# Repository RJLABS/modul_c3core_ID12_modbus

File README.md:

# modul_c3core_ID12_modbus

## Image Rendering

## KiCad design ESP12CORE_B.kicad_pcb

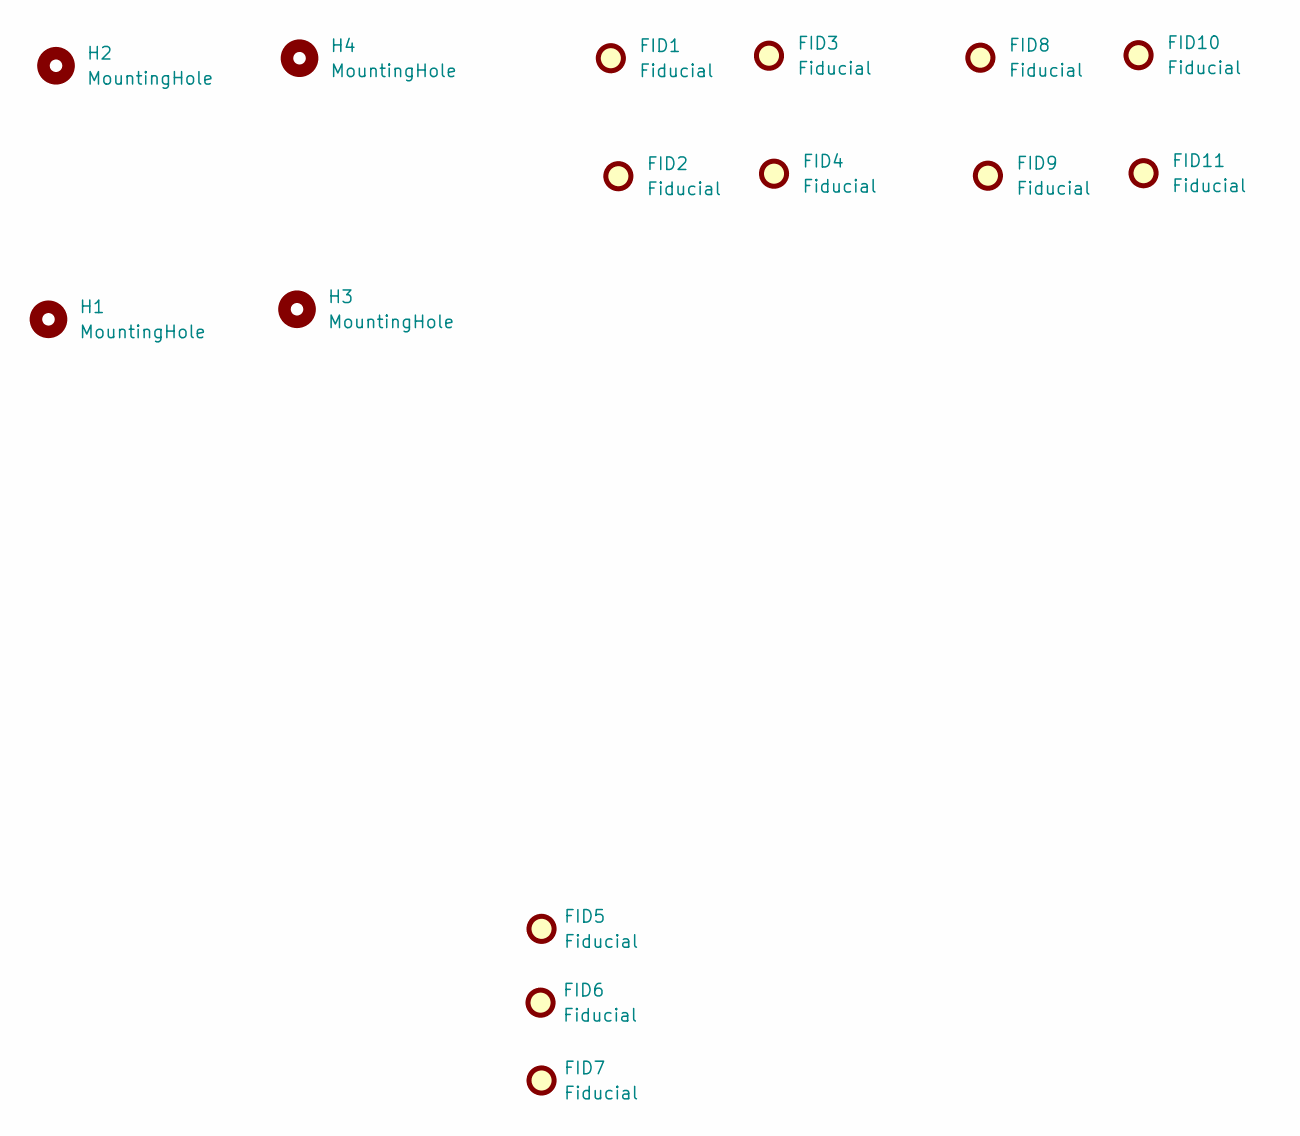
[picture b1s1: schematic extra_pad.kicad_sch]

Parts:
FID1, FID2, FID3, FID4, FID8, FID9, FID10, FID11: Fiducial; mouse-bite-2mm-slot
FID5, FID6, FID7: Fiducial; Fiducial_0.75mm_Mask1.5mm
H1, H2, H3, H4: MountingHole; MountingHole_3.2mm_M3_Pad_Via

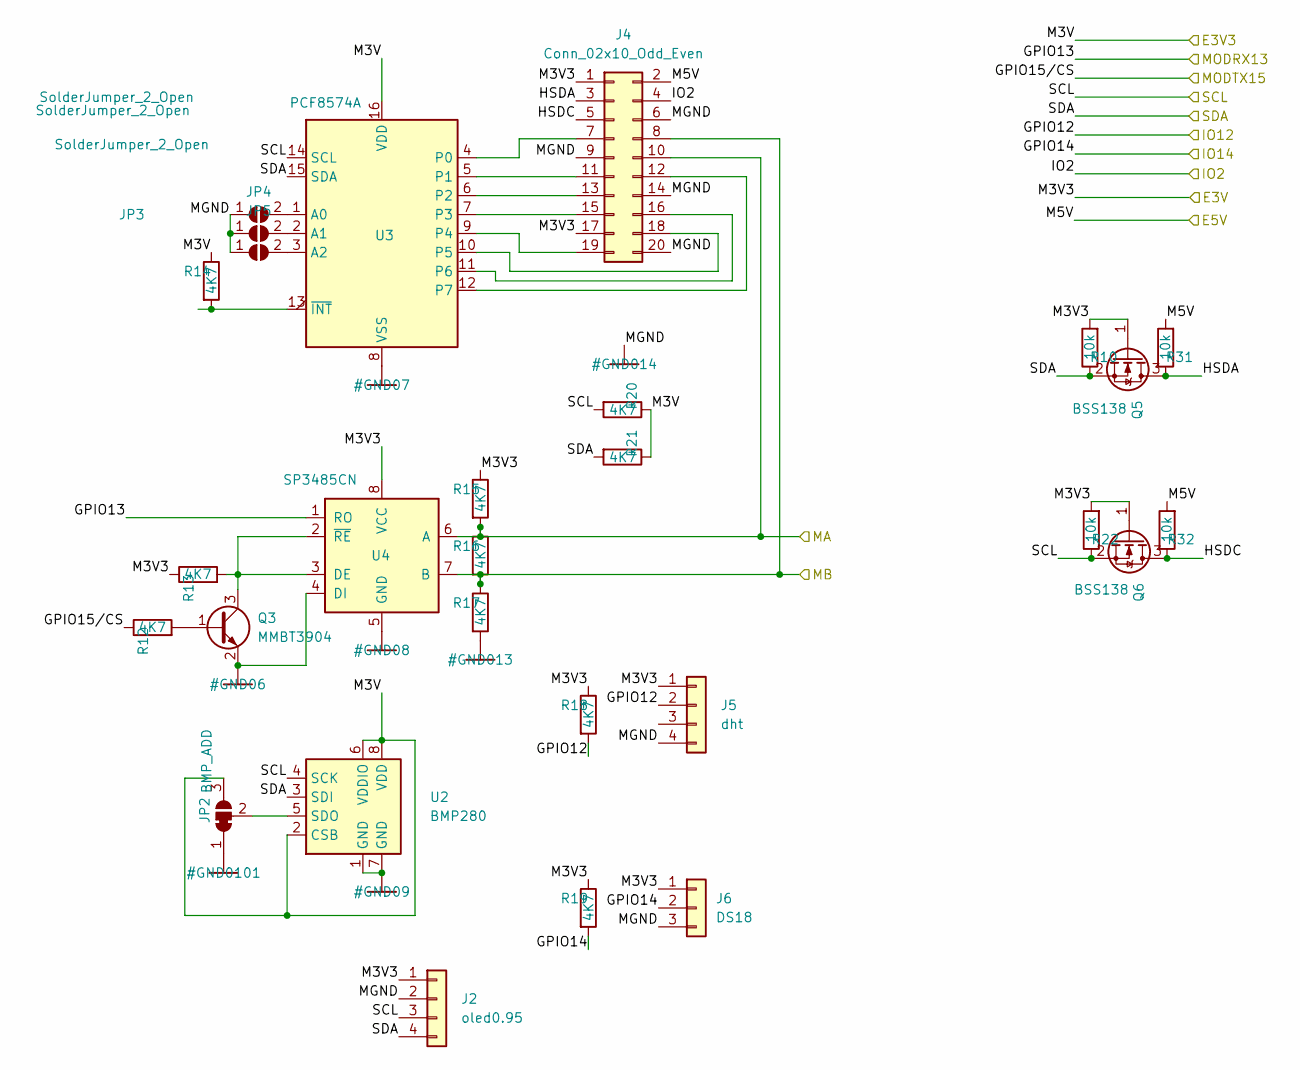
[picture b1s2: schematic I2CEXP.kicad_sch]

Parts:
J2: oled0.95; PinHeader_1x04_P2.54mm_Vertical
J4: Conn_02x10_Odd_Even; IDC-Header_2x10_P2.54mm_Vertical
J5: dht; PinHeader_1x04_P2.54mm_Vertical
J6: DS18; PinHeader_1x03_P2.54mm_Vertical
JP2: BMP_ADD; SolderJumper-3_P1.3mm_Bridged12_RoundedPad1.0x1.5mm
JP3, JP4, JP5: SolderJumper_2_Open; SolderJumper-2_P1.3mm_Open_RoundedPad1.0x1.5mm
Q3: MMBT3904; SOT-23
Q5, Q6: BSS138; SOT-23
R10, R22, R31, R32: 10k; R_0805_2012Metric
R12, R13, R14, R15, R16, R17, R18, R19, R20, R21: 4K7; R_0805_2012Metric
U2: BMP280; Bosch_LGA-8_2x2.5mm_P0.65mm_ClockwisePinNumbering
U3: PCF8574A; SOIC-16W_7.5x10.3mm_P1.27mm
U4: SP3485CN; SOIC-8_3.9x4.9mm_P1.27mm

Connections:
/CPU_ESP12F/EVCC: J2.1, J4.1, J4.17, J5.1, J6.1, Q5.1 (G), Q6.1 (G), R10.2, R13.1, R15.1, R18.1, R19.1, R22.2, U4.8 (VCC); also elsewhere on the board
/CPU_ESP12F/GPIO2: J4.4; also elsewhere on the board
/CPU_ESP12F/GPIO4/SDA: J2.4, Q5.2 (S), R10.1, R21.2, U2.3 (SDI), U3.15 (SDA); also elsewhere on the board
/CPU_ESP12F/GPIO5/SCL: J2.3, Q6.2 (S), R20.2, R22.1, U2.4 (SCK), U3.14 (SCL); also elsewhere on the board
/CPU_ESP12F/GPIO12/MISO: J5.2, R18.2; also elsewhere on the board
/CPU_ESP12F/GPIO13/MOSI: U4.1 (RO); also elsewhere on the board
/CPU_ESP12F/GPIO14/SCK: J6.2, R19.2; also elsewhere on the board
/CPU_ESP12F/GPIO15/CS: R12.1; also elsewhere on the board
/CPU_ESP12F/VCC: JP2.3 (B), R14.1, R20.1, R21.1, U2.2 (CSB), U2.6 (VDDIO), U2.8 (VDD), U3.16 (VDD); also elsewhere on the board
/EXTENTION/HSDA: J4.3, Q5.3 (D), R31.1
/EXTENTION/HSDC: J4.5, Q6.3 (D), R32.1
/EXTENTION/M5V: J4.2, R31.2, R32.2; also elsewhere on the board
/EXTENTION/MA: J4.10, R15.2, R16.1, U4.6 (A); also elsewhere on the board
/EXTENTION/MB: J4.8, R16.2, R17.1, U4.7 (B); also elsewhere on the board
GND: J2.2, J4.6, J4.9, J4.14, J4.20, J5.4, J6.3, JP2.1 (A), JP3.1 (A), JP4.1 (A), JP5.1 (A), Q3.2 (E), R17.2, U2.1 (GND), U2.7 (GND), U3.8 (VSS), U4.4 (DI), U4.5 (GND); also elsewhere on the board
unnamed: J4.7, U3.4 (P0)
unnamed: J4.11, U3.5 (P1)
unnamed: J4.12, U3.12 (P7)
unnamed: J4.13, U3.6 (P2)
unnamed: J4.15, U3.7 (P3)
unnamed: J4.16, U3.11 (P6)
unnamed: J4.18, U3.10 (P5)
unnamed: J4.19, U3.9 (P4)
unnamed: JP2.2 (C), U2.5 (SDO)
unnamed: JP3.2 (B), U3.1 (A0)
unnamed: JP4.2 (B), U3.2 (A1)
unnamed: JP5.2 (B), U3.3 (A2)
unnamed: Q3.1 (B), R12.2
unnamed: Q3.3 (C), R13.2, U4.2 (~RE), U4.3 (DE)
unnamed: R14.2, U3.13 (~INT)

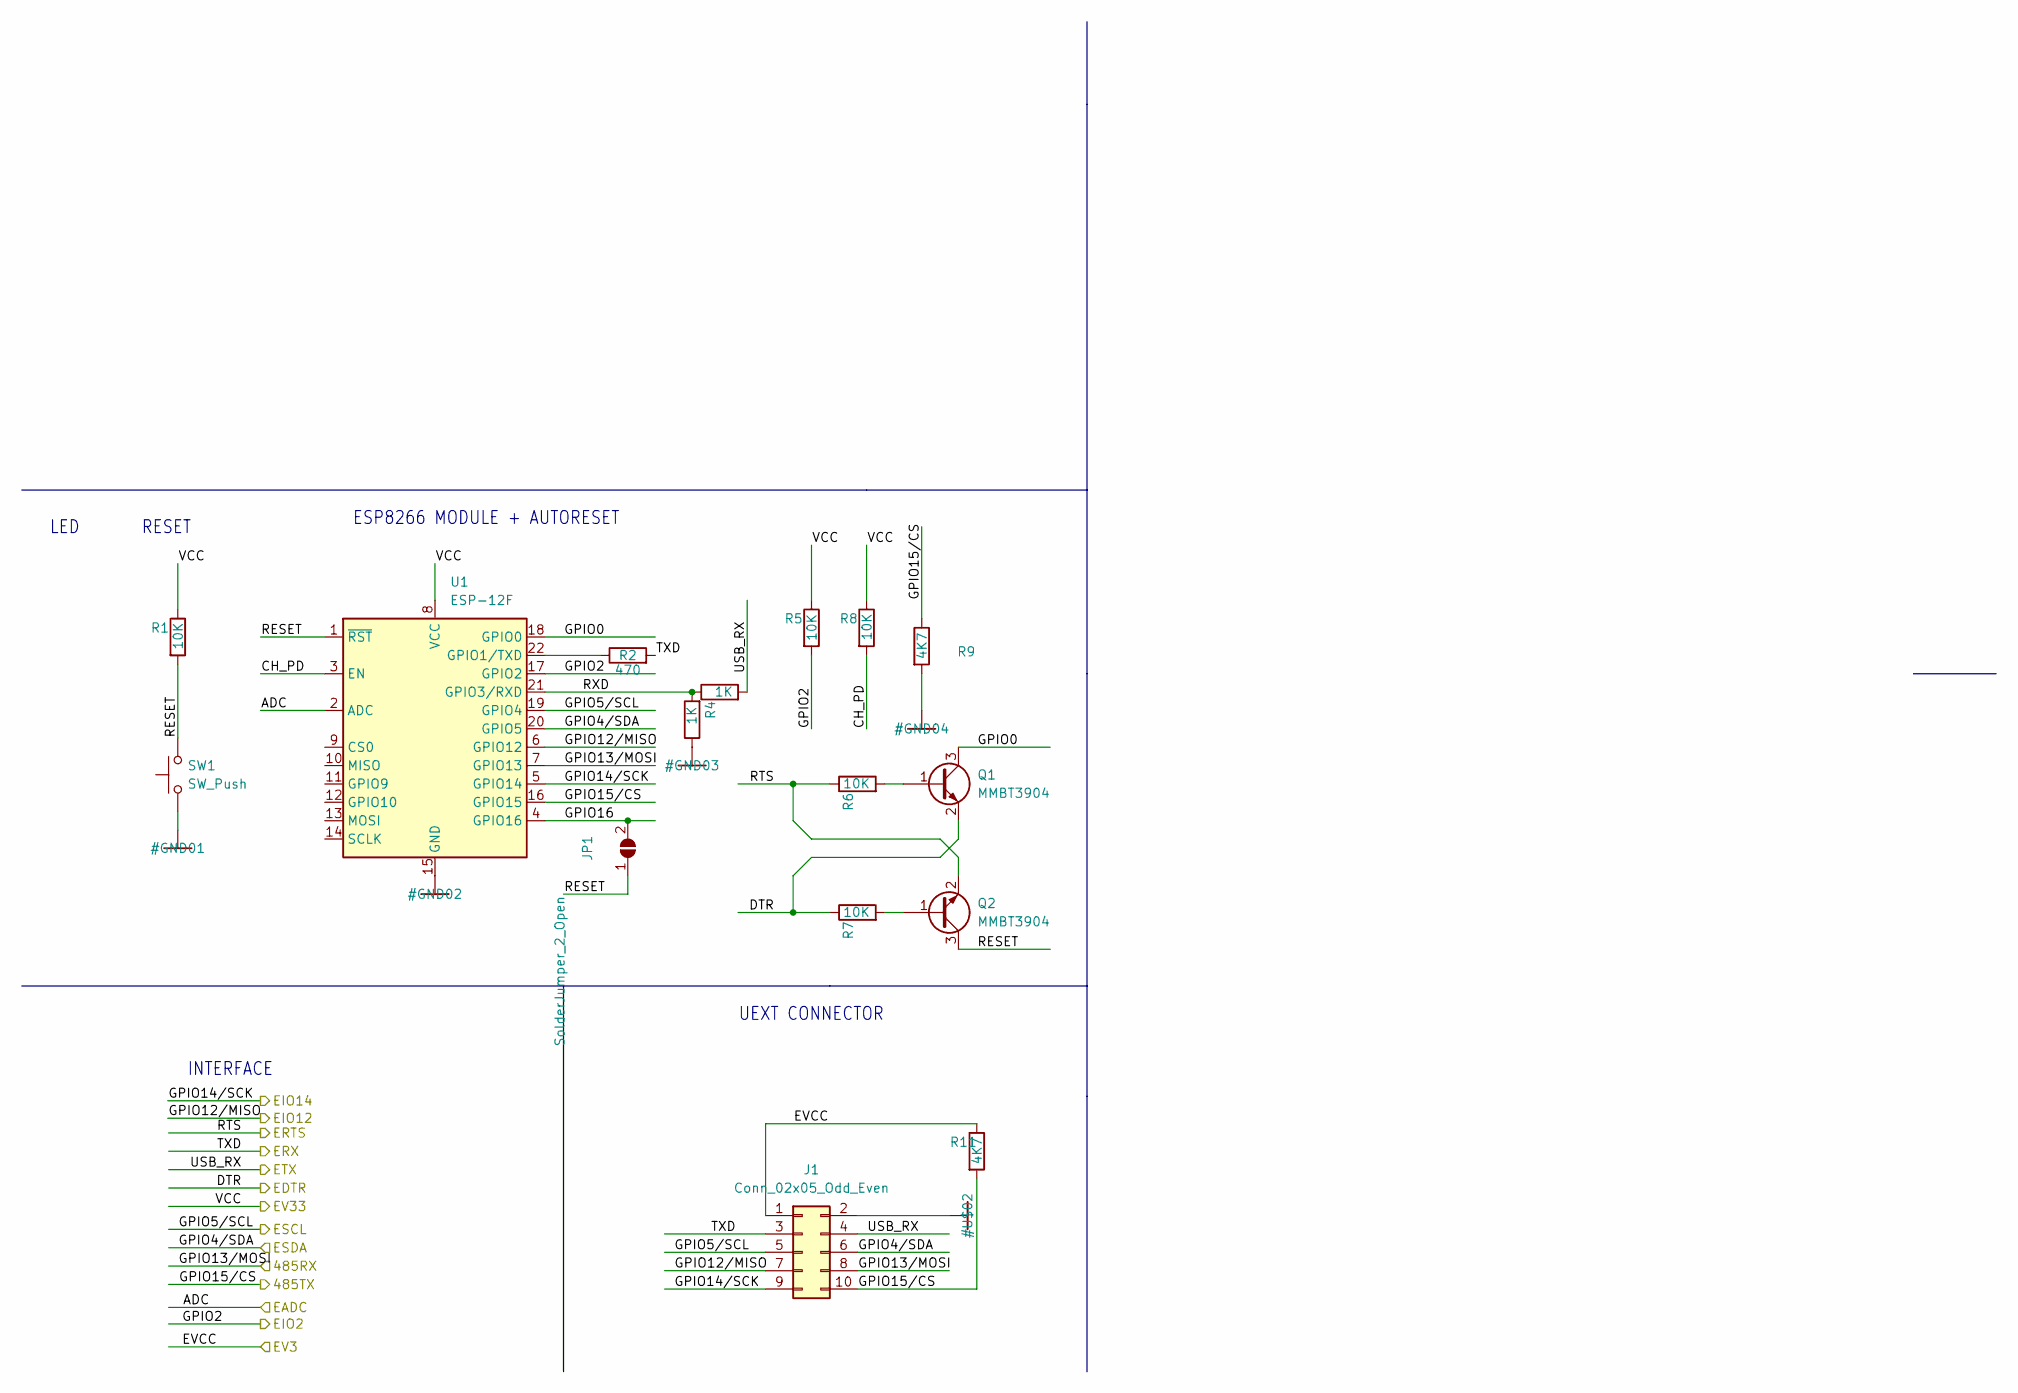
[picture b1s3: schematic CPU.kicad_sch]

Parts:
J1: Conn_02x05_Odd_Even; IDC-Header_2x05_P2.54mm_Vertical
JP1: SolderJumper_2_Open; SolderJumper-2_P1.3mm_Open_RoundedPad1.0x1.5mm
Q1, Q2: MMBT3904; SOT-23
R1, R5, R6, R7, R8: 10K; R_0805_2012Metric
R2: 470; R_0805_2012Metric
R3, R4: 1K; R_0805_2012Metric
R9, R11: 4K7; R_0805_2012Metric
SW1: SW_Push; SW_SPST_B3U-1000P-B
U1: ESP-12F; ESP-12E

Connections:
/CPU_ESP12F/ADC: U1.2 (ADC); also elsewhere on the board
/CPU_ESP12F/CH_PD: R8.2, U1.3 (EN)
/CPU_ESP12F/DTR: Q1.2 (E), R7.1; also elsewhere on the board
/CPU_ESP12F/EVCC: J1.1, R11.1; also elsewhere on the board
/CPU_ESP12F/GPIO0: Q1.3 (C), U1.18 (GPIO0)
/CPU_ESP12F/GPIO2: R5.2, U1.17 (GPIO2); also elsewhere on the board
/CPU_ESP12F/GPIO4/SDA: J1.6, U1.20 (GPIO5); also elsewhere on the board
/CPU_ESP12F/GPIO5/SCL: J1.5, U1.19 (GPIO4); also elsewhere on the board
/CPU_ESP12F/GPIO12/MISO: J1.7, U1.6 (GPIO12); also elsewhere on the board
/CPU_ESP12F/GPIO13/MOSI: J1.8, U1.7 (GPIO13); also elsewhere on the board
/CPU_ESP12F/GPIO14/SCK: J1.9, U1.5 (GPIO14); also elsewhere on the board
/CPU_ESP12F/GPIO15/CS: J1.10, R9.1, R11.2, U1.16 (GPIO15); also elsewhere on the board
/CPU_ESP12F/GPIO16: JP1.2 (B), U1.4 (GPIO16)
/CPU_ESP12F/RXD: R3.2, R4.1, U1.21 (GPIO3/RXD)
/CPU_ESP12F/TXD: J1.3, R2.2; also elsewhere on the board
/CPU_ESP12F/USB_RX: J1.4, R4.2; also elsewhere on the board
/CPU_ESP12F/VCC: R1.1, R5.1, R8.1, U1.8 (VCC); also elsewhere on the board
GND: J1.2, R3.1, R9.2, SW1.1, U1.15 (GND); also elsewhere on the board
unnamed: Q1.1 (B), R6.2
unnamed: Q2.1 (B), R7.2
unnamed: R2.1, U1.22 (GPIO1/TXD)

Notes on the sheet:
UEXT CONNECTOR
LED
INTERFACE
ESP8266 MODULE + AUTORESET
RESET

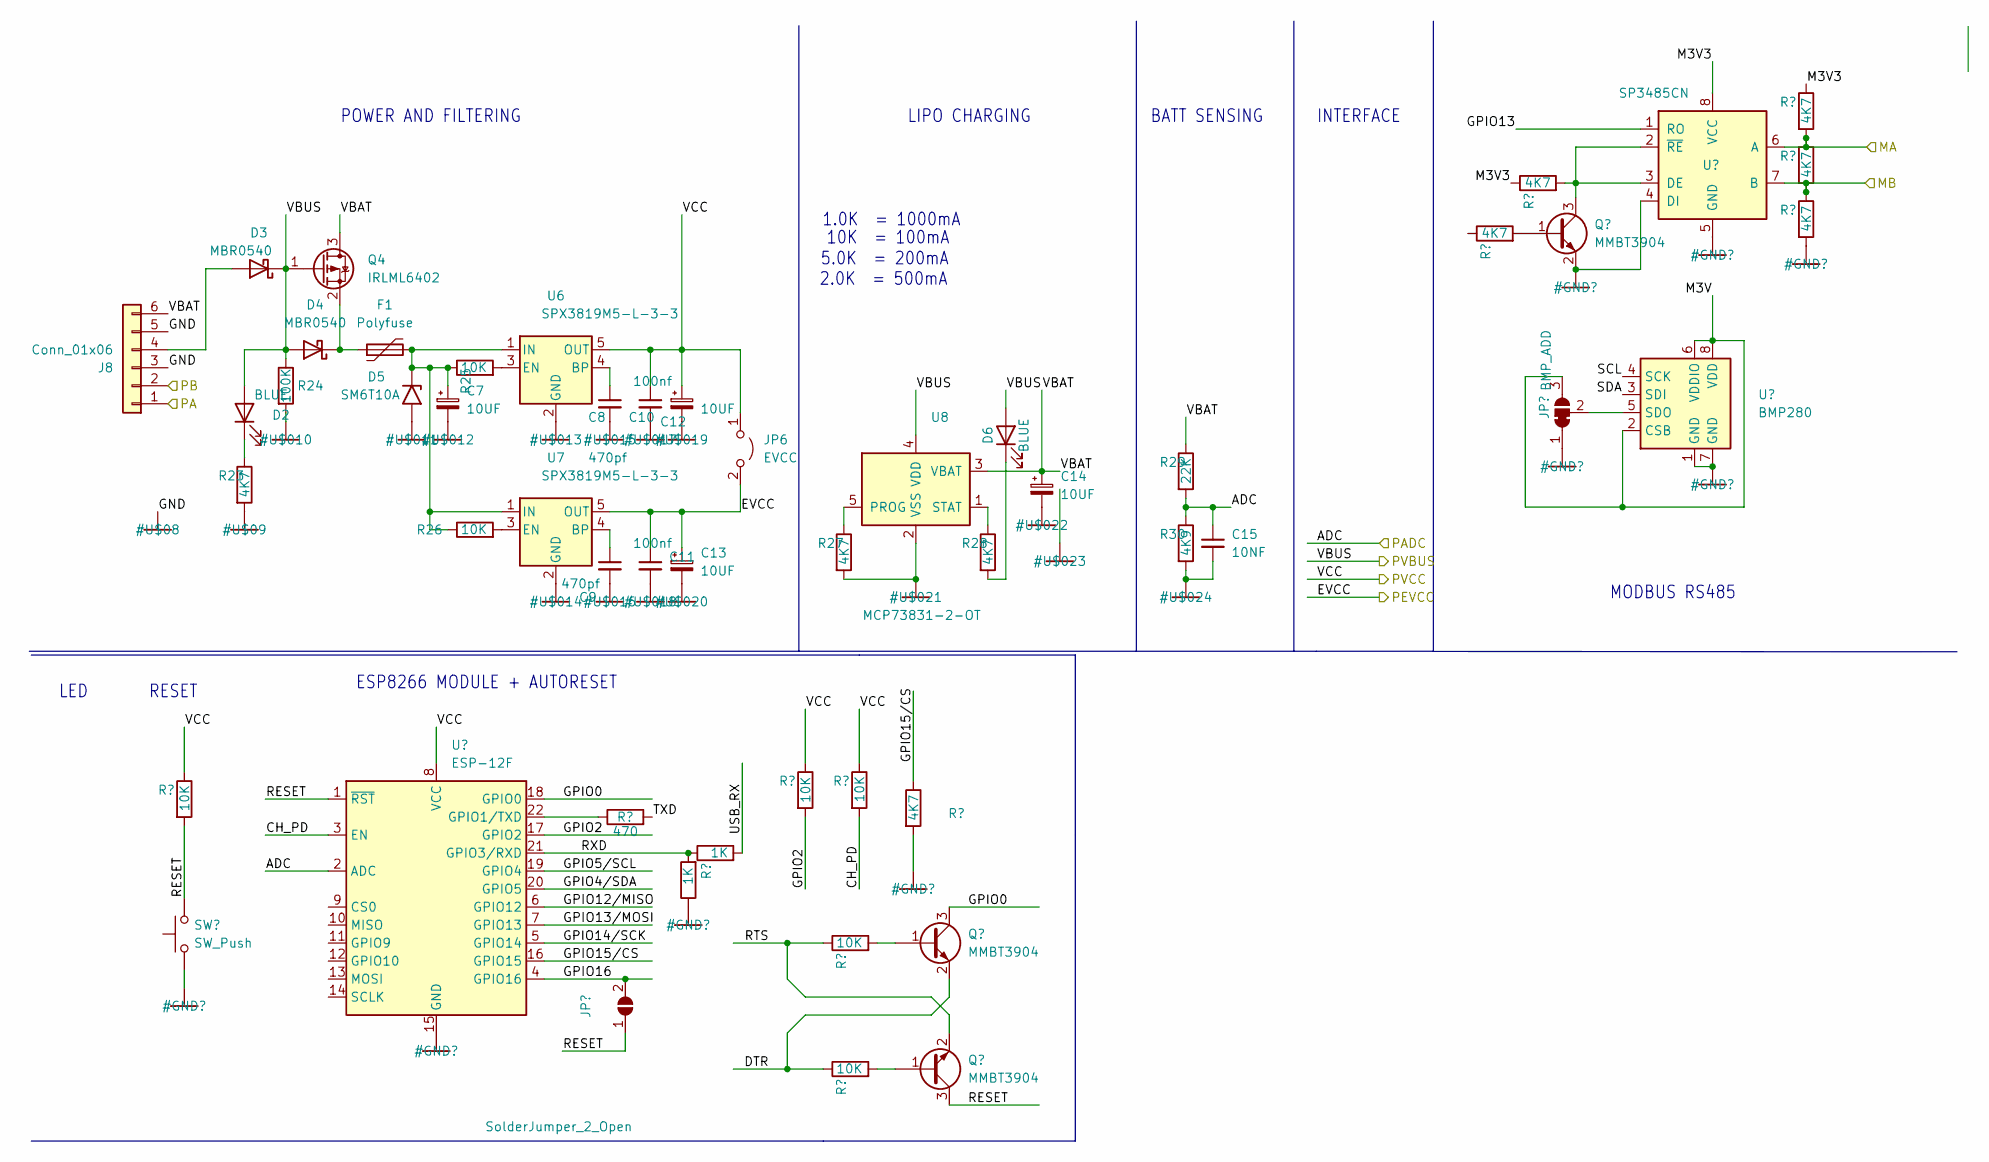
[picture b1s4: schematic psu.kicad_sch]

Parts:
C7, C12: 10UF; CP_Elec_5x4.4
C8, C9: 470pf; C_0805_2012Metric
C10, C11: 100nf; C_0805_2012Metric
C13: 10UF; C_1812_4532Metric
C14: 10UF; C_1206_3216Metric
C15: 10NF; C_0805_2012Metric
D2, D6: BLUE; D_0805_2012Metric
D3, D4: MBR0540; D_SOD-123
D5: SM6T10A; D_SMB
F1: Polyfuse; Fuse_1210_3225Metric
J8: Conn_01x06; TerminalBlock_bornier-6_P5.08mm
JP6: EVCC; SolderJumper-2_P1.3mm_Bridged_RoundedPad1.0x1.5mm
Q4: IRLML6402; SOT-23
R23, R27, R28: 4K7; R_0805_2012Metric
R24: 100K; R_0805_2012Metric
R25, R26: 10K; R_0805_2012Metric
R29: 22K; R_0805_2012Metric
R30: 4K9; R_0805_2012Metric
U6, U7: SPX3819M5-L-3-3; SOT-23-5
U8: MCP73831-2-OT; SOT-23-5

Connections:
/CPU_ESP12F/ADC: C15.1, R29.2, R30.1; also elsewhere on the board
/CPU_ESP12F/EVCC: C11.1, C13.1, JP6.2 (B), U7.5 (OUT); also elsewhere on the board
/CPU_ESP12F/VCC: C10.1, C12.1, JP6.1 (A), U6.5 (OUT); also elsewhere on the board
/EXTENTION/M5V: D2.2 (A), D3.1 (K), D4.2 (A), D6.2 (A), Q4.1 (G), R24.1, U8.4 (VDD); also elsewhere on the board
/EXTENTION/MA: J8.1; also elsewhere on the board
/EXTENTION/MB: J8.2; also elsewhere on the board
/psu/VBAT: C14.1, J8.6, Q4.3 (D), R29.1, U8.3 (VBAT)
GND: C7.2, C8.2, C9.2, C10.2, C11.2, C12.2, C13.2, C14.2, C15.2, D5.2 (A2), J8.3, J8.5, R23.2, R24.2, R27.2, R30.2, U6.2 (GND), U7.2 (GND), U8.2 (VSS); also elsewhere on the board
unnamed: C7.1, D5.1 (A1), F1.2, R25.1, R26.1, U6.1 (IN), U7.1 (IN)
unnamed: C8.1, U6.4 (BP)
unnamed: C9.1, U7.4 (BP)
unnamed: D2.1 (K), R23.1
unnamed: D3.2 (A), J8.4
unnamed: D4.1 (K), F1.1, Q4.2 (S)
unnamed: D6.1 (K), R28.2
unnamed: R25.2, U6.3 (EN)
unnamed: R26.2, U7.3 (EN)
unnamed: R27.1, U8.5 (PROG)
unnamed: R28.1, U8.1 (STAT)

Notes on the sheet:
INTERFACE
ESP8266 MODULE + AUTORESET
POWER AND FILTERING
BATT SENSING
2.0K = 500mA
1.0K = 1000mA
RESET
MODBUS RS485
LIPO CHARGING
10K = 100mA
LED
5.0K = 200mA

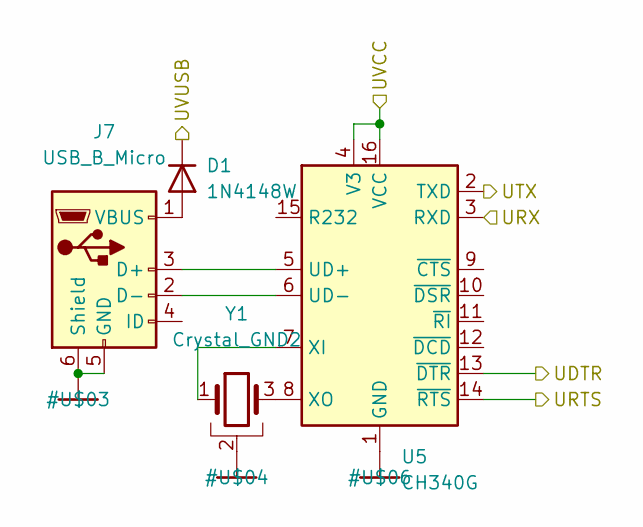
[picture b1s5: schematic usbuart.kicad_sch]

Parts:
D1: 1N4148W; D_SOD-123
J7: USB_B_Micro; USB_Micro-B_Wuerth_629105150521
U5: CH340G; SOIC-16_3.9x9.9mm_P1.27mm
Y1: Crystal_GND2; Resonator_SMD_Murata_CSTxExxV-3Pin_3.0x1.1mm

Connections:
/CPU_ESP12F/DTR: U5.13 (~DTR); also elsewhere on the board
/CPU_ESP12F/TXD: U5.3 (RXD); also elsewhere on the board
/CPU_ESP12F/USB_RX: U5.2 (TXD); also elsewhere on the board
/CPU_ESP12F/VCC: U5.4 (V3), U5.16 (VCC); also elsewhere on the board
/EXTENTION/M5V: D1.1 (K); also elsewhere on the board
GND: J7.5 (GND), J7.6 (Shield), U5.1 (GND), Y1.2; also elsewhere on the board
unnamed: D1.2 (A), J7.1 (VBUS)
unnamed: J7.2 (D-), U5.6 (UD-)
unnamed: J7.3 (D+), U5.5 (UD+)
unnamed: U5.7 (XI), Y1.1
unnamed: U5.8 (XO), Y1.3

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
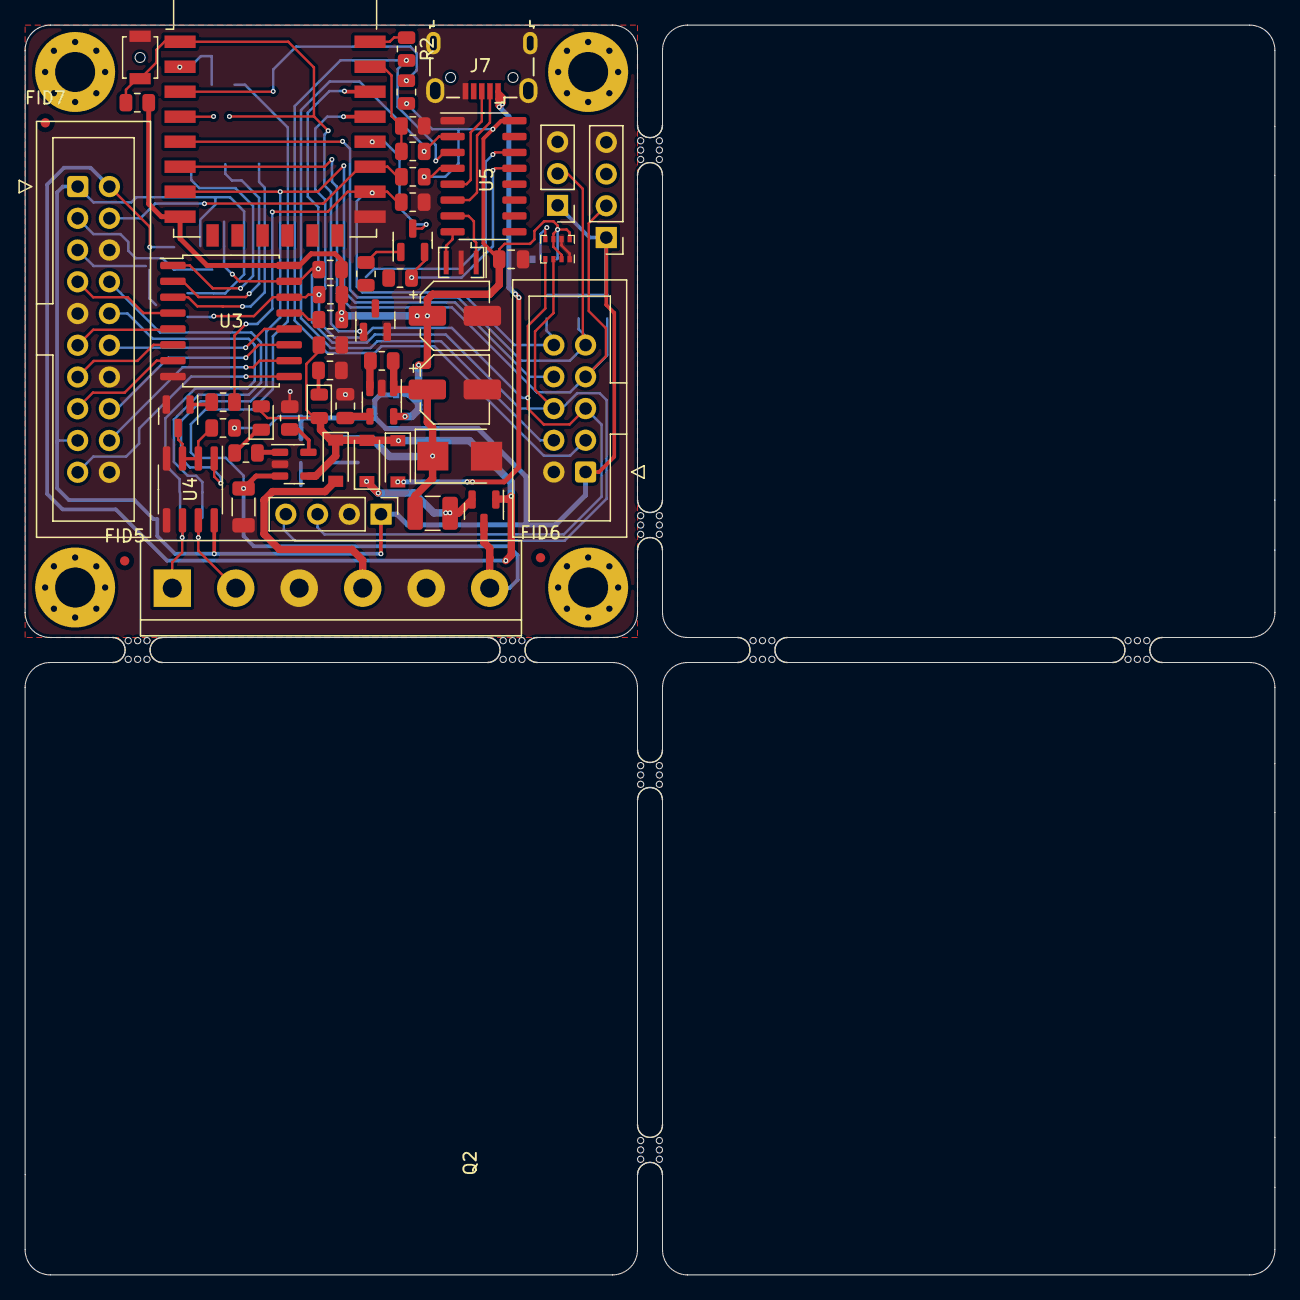
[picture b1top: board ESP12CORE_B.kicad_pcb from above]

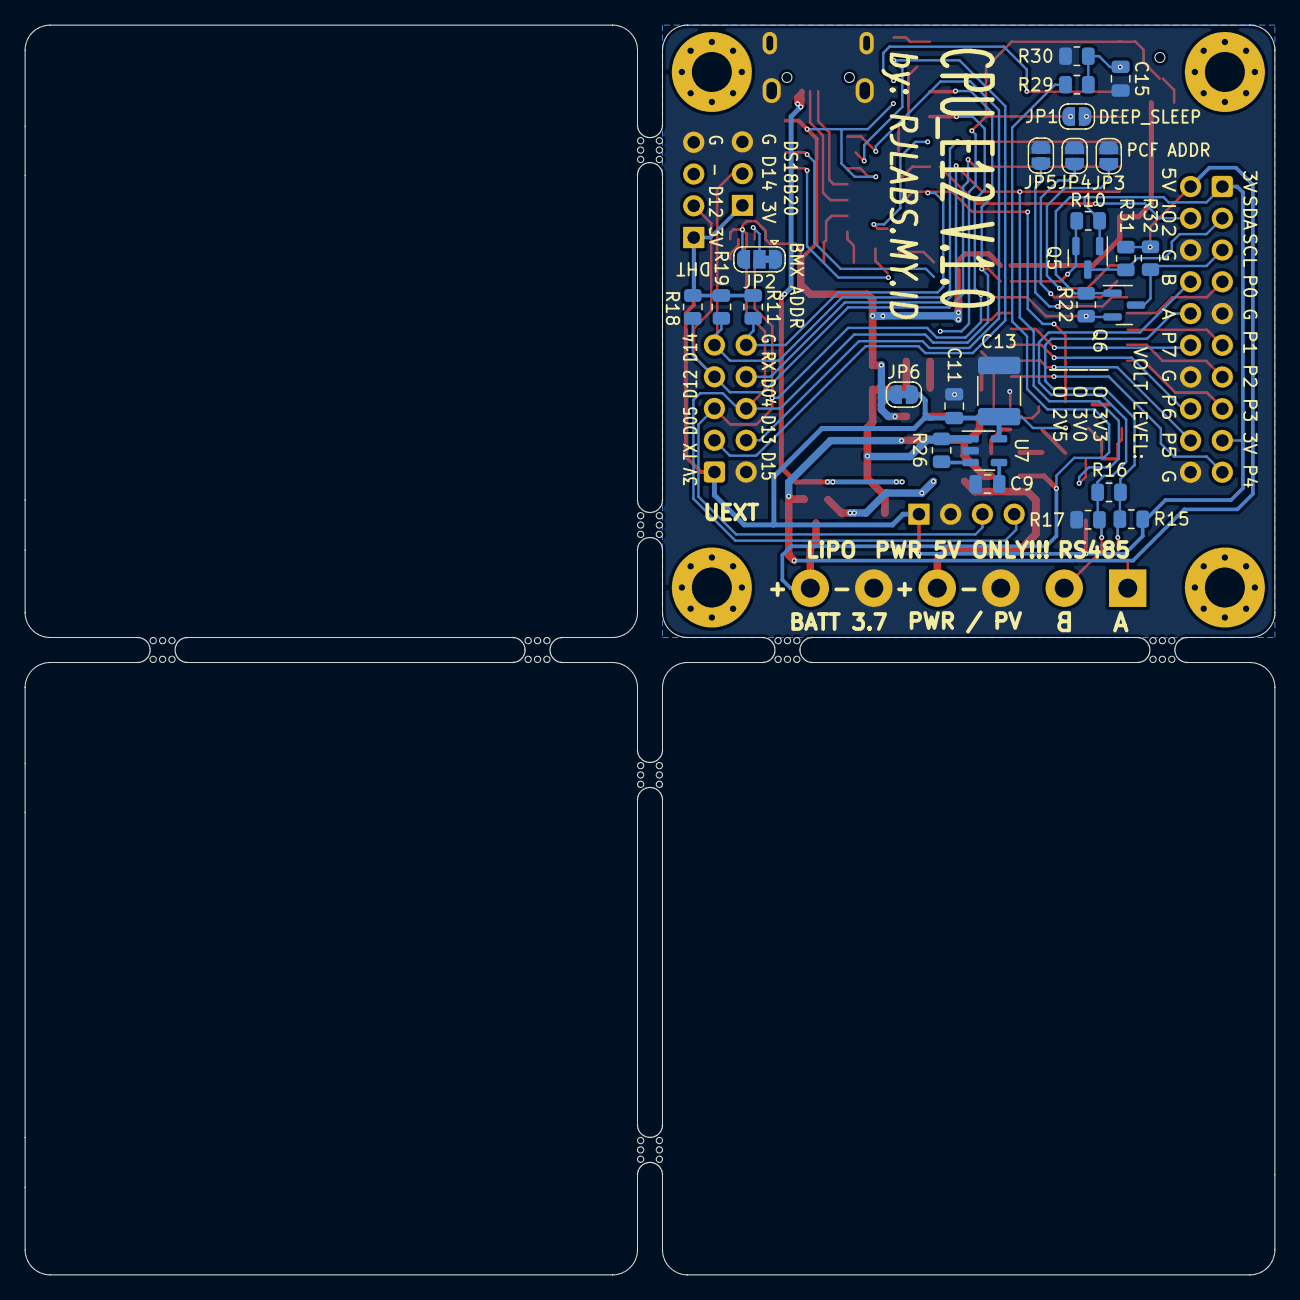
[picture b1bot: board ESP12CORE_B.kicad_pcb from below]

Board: 2 copper layers, 99.9 x 99.9 mm, 92 parts (26 on the bottom side), 60 nets.
